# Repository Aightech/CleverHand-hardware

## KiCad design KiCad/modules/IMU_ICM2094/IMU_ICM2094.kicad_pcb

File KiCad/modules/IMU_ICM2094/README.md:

# IMU ICM2094 Module
This module is an Inertial Measurement Unit (IMU) that embeds the ICM2094 sensor. It is responsible for acquiring the acceleration, angular velocity and magnetic field signals.

## Electrical Schematic

## PCB Layout

## 3D Model

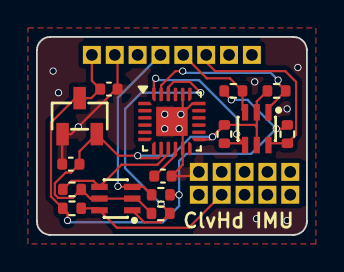
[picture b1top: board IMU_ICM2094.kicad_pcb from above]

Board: 4 copper layers, 15.0 x 11.0 mm, 34 parts (1 on the bottom side), 12 nets.

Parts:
C1, C2: 1uF; C_0402_1005Metric
C5: 100nF; C_0402_1005Metric
J1, J2, J3, J4, J5, J6, J7, J8, J9, J10, J11, J12, J13, J14, J15, J16, J17, J18: Conn_01x01_Pin; PinHeader_1x01_P1.27mm_Vertical
R1, R2, R3, R4, R5, R6, R7, R8: 4.7k; R_0402_1005Metric
U1: MCP1700T-1802E/TT; SOT-23-3_L2.9-W1.3-P1.90-LS2.4-BR
U3, U5: BSS138BKS; SOT-363_L2.1-W1.3-P0.65-LS2.3-BL
U4: ICM-20948; QFN-24-1EP_3x3mm_P0.4mm_EP1.75x1.6mm
kibuzzard-66093797: G***; kibuzzard-66093797

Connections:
+3.3V: C1.1, J1.1, R1.1, R4.1, R5.1, R8.1, U1.3 (VIN)
/1.8V: C2.1, R2.2, R3.1, R6.2, R7.1, U1.2 (VOUT), U3.2 (G2), U3.5 (G1), U4.8 (VDDIO), U4.13 (VDD), U5.2 (G2), U5.5 (G1)
/CSB: J17.1, R8.2, U5.6 (D2)
/CS_1.8V: R7.2, U4.22 (nCS), U5.1 (S2)
/MISO: J4.1, R5.2, U5.3 (D1)
/MISO_1.8V: R6.1, U4.9 (SDO/AD0), U5.4 (S1)
/MOSI: J5.1, R1.2, U3.3 (D1)
/MOSI_1.8V: R2.1, U3.4 (S1), U4.24 (SDA/SDI)
/SCK_1.8V: R3.2, U3.1 (S2), U4.23 (SCL/SCLK)
/SCLK: J6.1, R4.2, U3.6 (D2)
GND: C1.2, C2.2, C5.2, J2.1, J18.1, U1.1 (GND), U4.11 (FSYNC), U4.18 (GND), U4.20 (RESV), U4.25 (EP)
unnamed: C5.1, U4.10 (REGOUT)

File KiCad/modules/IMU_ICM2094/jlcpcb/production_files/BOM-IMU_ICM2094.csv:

Comment,Designator,Footprint,LCSC
MCP1700T-1802E/TT,U1,SOT-23-3_L2.9-W1.3-P1.90-LS2.4-BR,C150796
100nF,C5,C_0402_1005Metric,C1525
BSS138BKS,"U3,U5",SOT-363_L2.1-W1.3-P0.65-LS2.3-BL,C5224290
1uF,C2,C_0402_1005Metric,C52923
ICM-20948,U4,QFN-24-1EP_3x3mm_P0.4mm_EP1.75x1.6mm,C726001
Conn_01x01_Pin,J3,PinHeader_1x01_P1.27mm_Vertical,
Conn_01x01_Pin,J1,PinHeader_1x01_P1.27mm_Vertical,
Conn_01x01_Pin,J2,PinHeader_1x01_P1.27mm_Vertical,
Conn_01x01_Pin,J9,PinHeader_1x01_P1.27mm_Vertical,
Conn_01x01_Pin,J15,PinHeader_1x01_P1.27mm_Vertical,
Conn_01x01_Pin,J7,PinHeader_1x01_P1.27mm_Vertical,
Conn_01x01_Pin,J5,PinHeader_1x01_P1.27mm_Vertical,
Conn_01x01_Pin,J4,PinHeader_1x01_P1.27mm_Vertical,
Conn_01x01_Pin,J10,PinHeader_1x01_P1.27mm_Vertical,
Conn_01x01_Pin,J14,PinHeader_1x01_P1.27mm_Vertical,
Conn_01x01_Pin,J8,PinHeader_1x01_P1.27mm_Vertical,
Conn_01x01_Pin,J12,PinHeader_1x01_P1.27mm_Vertical,
Conn_01x01_Pin,J16,PinHeader_1x01_P1.27mm_Vertical,
Conn_01x01_Pin,J6,PinHeader_1x01_P1.27mm_Vertical,
Conn_01x01_Pin,J11,PinHeader_1x01_P1.27mm_Vertical,
Conn_01x01_Pin,J13,PinHeader_1x01_P1.27mm_Vertical,
4.7k,R1,R_0402_1005Metric,
1uF,C1,C_0402_1005Metric,
4.7k,R2,R_0402_1005Metric,
Conn_01x01_Pin,J18,PinHeader_1x01_P1.27mm_Vertical,
Conn_01x01_Pin,J17,PinHeader_1x01_P1.27mm_Vertical,
4.7k,R7,R_0402_1005Metric,
4.7k,R5,R_0402_1005Metric,
4.7k,R3,R_0402_1005Metric,
4.7k,R8,R_0402_1005Metric,
4.7k,R4,R_0402_1005Metric,
4.7k,R6,R_0402_1005Metric,

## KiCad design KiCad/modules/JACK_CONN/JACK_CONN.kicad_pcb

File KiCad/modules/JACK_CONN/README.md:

# Communication Module
This module is responsible for handling the communication between the different modules of the master node.

The communication bus is composed of :
- Power supply (3.3V) and ground
- SPI bus (MISO, MOSI, SCK)
- I2C bus (SDA, SCL)
- Address bus (A0, A1, A2, A3, A4)
- External reference voltage (AREF)

When the module is connected to the bus, it is assigned an address by the master node. This address is used to identify the module on the bus.
The communication module will will activate the chip select line of the associated sensor module when the address bus matches its address.
Additionally, each module has a unique identifier that is used to identify the module on the I2C bus.

## Electrical Schematic

## PCB Layout

## 3D Model

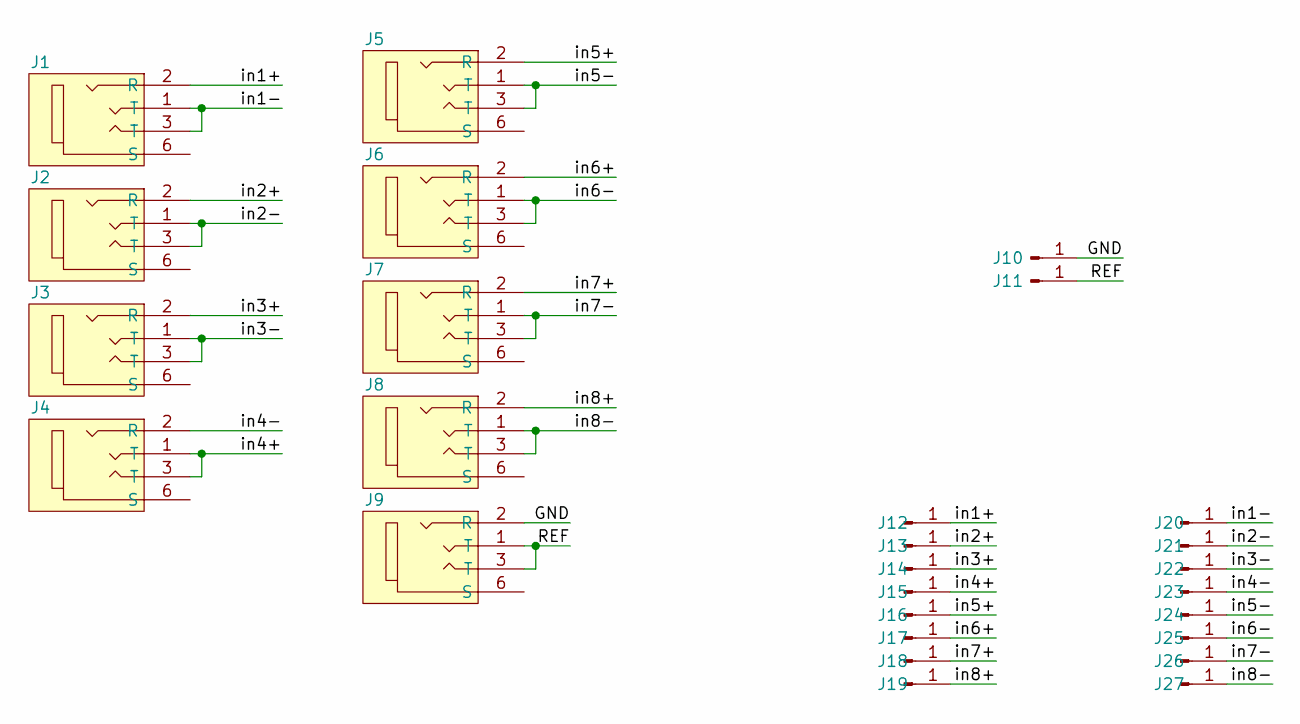
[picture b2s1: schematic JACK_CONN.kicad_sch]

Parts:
J1, J2, J3, J4, J5, J6, J7, J8, J9: jack2.5_PJ-210B; Jack_Socket_PJ-210B
J10, J11: Conn_01x01_Pin; PinHeader_1x01_P2.54mm_Vertical
J12, J13, J14, J15, J16, J17, J18, J19, J20, J21, J22, J23, J24, J25, J26, J27: Conn_01x01_Pin; Pin_D1.2mm_pogo

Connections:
/GND: J9.2 (R), J10.1
/REF: J9.1 (T), J9.3 (T), J11.1
/in1+: J1.2 (R), J12.1
/in1-: J1.1 (T), J1.3 (T), J20.1
/in2+: J2.2 (R), J13.1
/in2-: J2.1 (T), J2.3 (T), J21.1
/in3+: J3.2 (R), J14.1
/in3-: J3.1 (T), J3.3 (T), J22.1
/in4+: J4.1 (T), J4.3 (T), J15.1
/in4-: J4.2 (R), J23.1
/in5+: J5.2 (R), J16.1
/in5-: J5.1 (T), J5.3 (T), J24.1
/in6+: J6.2 (R), J17.1
/in6-: J6.1 (T), J6.3 (T), J25.1
/in7+: J7.2 (R), J18.1
/in7-: J7.1 (T), J7.3 (T), J26.1
/in8+: J8.2 (R), J19.1
/in8-: J8.1 (T), J8.3 (T), J27.1

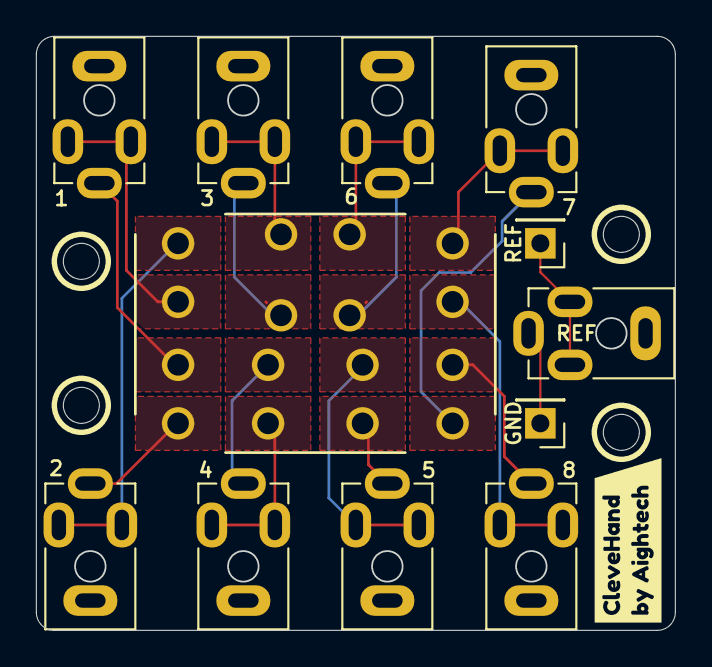
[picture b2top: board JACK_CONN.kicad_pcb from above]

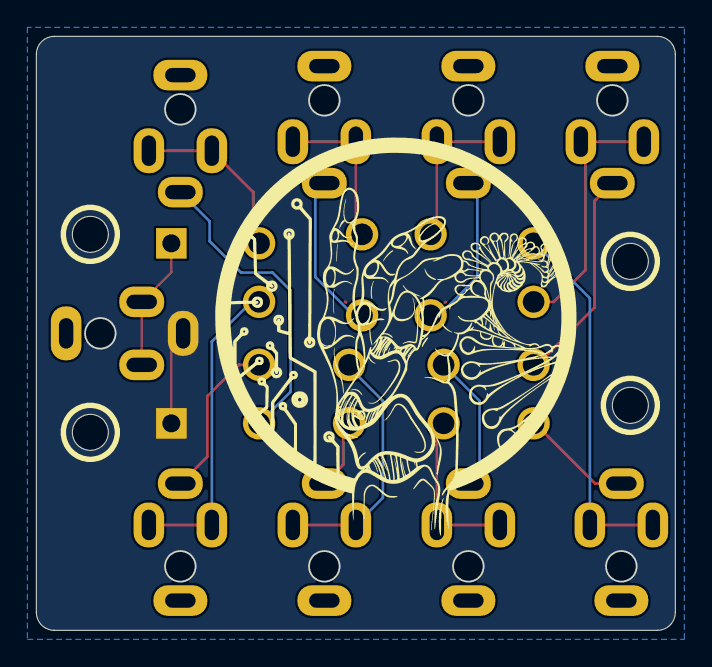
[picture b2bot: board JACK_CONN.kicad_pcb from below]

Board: 4 copper layers, 35.5 x 33.0 mm, 28 parts (16 on the bottom side), 18 nets.

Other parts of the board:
kibuzzard-6607178A: G***; kibuzzard-6607178A

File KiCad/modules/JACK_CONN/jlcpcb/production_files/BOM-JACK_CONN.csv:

Comment,Designator,Footprint,LCSC
Conn_01x01_Pin,J13,Pin_D1.2mm_pogo,
Conn_01x01_Pin,J12,Pin_D1.2mm_pogo,
Conn_01x01_Pin,J11,PinHeader_1x01_P2.54mm_Vertical,
Conn_01x01_Pin,J10,PinHeader_1x01_P2.54mm_Vertical,
jack2.5_PJ-210B,J9,Jack_Socket_PJ-210B,
Conn_01x01_Pin,J15,Pin_D1.2mm_pogo,
Conn_01x01_Pin,J14,Pin_D1.2mm_pogo,
jack2.5_PJ-210B,J6,Jack_Socket_PJ-210B,
jack2.5_PJ-210B,J3,Jack_Socket_PJ-210B,
jack2.5_PJ-210B,J1,Jack_Socket_PJ-210B,
jack2.5_PJ-210B,J4,Jack_Socket_PJ-210B,
jack2.5_PJ-210B,J2,Jack_Socket_PJ-210B,
jack2.5_PJ-210B,J5,Jack_Socket_PJ-210B,
jack2.5_PJ-210B,J7,Jack_Socket_PJ-210B,
jack2.5_PJ-210B,J8,Jack_Socket_PJ-210B,
Conn_01x01_Pin,J25,Pin_D1.2mm_pogo,
Conn_01x01_Pin,J21,Pin_D1.2mm_pogo,
Conn_01x01_Pin,J20,Pin_D1.2mm_pogo,
Conn_01x01_Pin,J18,Pin_D1.2mm_pogo,
Conn_01x01_Pin,J23,Pin_D1.2mm_pogo,
Conn_01x01_Pin,J16,Pin_D1.2mm_pogo,
Conn_01x01_Pin,J27,Pin_D1.2mm_pogo,
Conn_01x01_Pin,J24,Pin_D1.2mm_pogo,
Conn_01x01_Pin,J26,Pin_D1.2mm_pogo,
Conn_01x01_Pin,J17,Pin_D1.2mm_pogo,
Conn_01x01_Pin,J22,Pin_D1.2mm_pogo,
Conn_01x01_Pin,J19,Pin_D1.2mm_pogo,

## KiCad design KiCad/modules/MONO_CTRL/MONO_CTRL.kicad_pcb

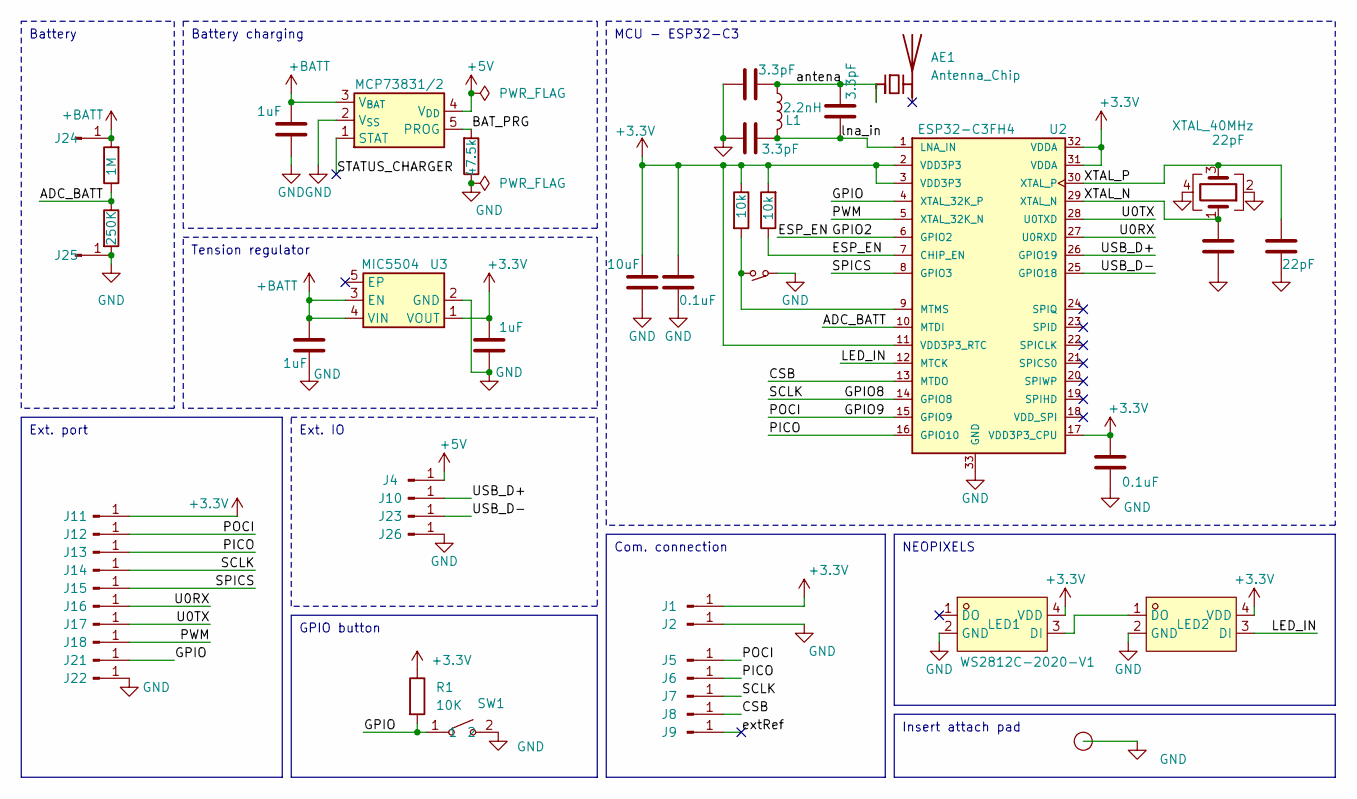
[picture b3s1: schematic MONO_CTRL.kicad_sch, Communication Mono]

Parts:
AE1: Antenna_Chip; C_1206_3216Metric; LCSC C6807751
C1, C3, C12: 3.3pF; C_0402_1005Metric
C2, C8, C9: 1uF; C_0402_1005Metric
C4: 22pF; C_0402_1005Metric; LCSC C12530
C5: 22pF; C_0402_1005Metric; LCSC C1532
C6: 10uF; C_0402_1005Metric
C7, C10: 0.1uF; C_0402_1005Metric
I1: smd_insert; insert_1.2mm
J1, J2, J4, J5, J6, J7, J8, J9, J10, J11, J12, J13, J14, J15, J16, J17, J18, J21, J22, J23, J24, J25, J26: Conn_01x01_Pin; PinHeader_1x01_P1.27mm_Vertical
L1: 2.2nH; L_0402_1005Metric
LED1: WS2812C-2020-V1; LED-SMD_4P-L2.0-W2.0-TL_WS2812B-2020; LCSC Part C2976072
LED2: WS2812C; LED-SMD_4P-L2.0-W2.0-TL_WS2812B-2020; LCSC Part C2976072
R1: 10K; R_0402_1005Metric; LCSC C25744
R2: 47.5k; R_0402_1005Metric; LCSC C25762
R3: 1M; R_0402_1005Metric; LCSC C25762
R4, R5: 10k; R_0402_1005Metric; LCSC C25762
R6: 250K; R_0402_1005Metric; LCSC C25762
SW1: TS-1088R-02026; SW-SMD_L3.9-W3.0-P4.45; LCSC Part C455280
SW2: SW-SMD_L3.9-W3.0-P4.45; LCSC C720477
U1: MCP73831/2; SOT-23-5; LCSC C14879
U2: ESP32-C3FH4; PARTREV V1.0; LCSC C2858491
U3: MIC5504; UDFN-4-1EP_1x1mm_P0.65mm_EP0.48x0.48mm; LCSC C3021135
Y1: XTAL_40MHz; Crystal_SMD_2016-4Pin_2.0x1.6mm; LCSC C2929402

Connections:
+3.3V: C6.1, C7.1, C9.1, C10.1, J1.1, J11.1, LED1.4 (VDD), LED2.4 (VDD), R1.1, R4.1, R5.2, U2.2 (VDD3P3), U2.3 (VDD3P3), U2.11 (VDD3P3_RTC), U2.17 (VDD3P3_CPU), U2.31 (VDDA), U2.32 (VDDA), U3.1 (VOUT)
+5V: J4.1, U1.4 (V_{DD})
+BATT: C2.1, C8.1, J24.1, R3.2, U1.3 (V_{BAT}), U3.3 (EN), U3.4 (VIN)
/ADC_BATT: R3.1, R6.1, U2.10 (MTDI)
/BAT_PRG: R2.2, U1.5 (PROG)
/CSB: J8.1, U2.13 (MTDO)
/ESP_EN: R5.1, U2.6 (GPIO2), U2.7 (CHIP_EN)
/GPIO: J21.1, R1.2, SW1.1, U2.4 (XTAL_32K_P)
/GPIO8: J7.1, J14.1, U2.14 (GPIO8)
/GPIO9: J5.1, J12.1, U2.15 (GPIO9)
/LED_IN: LED2.3 (DI), U2.12 (MTCK)
/PICO: J6.1, J13.1, U2.16 (GPIO10)
/PWM: J18.1, U2.5 (XTAL_32K_N)
/SPICS: J15.1, U2.8 (GPIO3)
/STATUS_CHARGER: U1.1 (STAT)
/U0RX: J16.1, U2.27 (U0RXD)
/U0TX: J17.1, U2.28 (U0TXD)
/USB_D+: J10.1, U2.26 (GPIO19)
/USB_D-: J23.1, U2.25 (GPIO18)
/XTAL_N: C4.1, U2.29 (XTAL_N), Y1.1
/XTAL_P: C5.1, U2.30 (XTAL_P), Y1.3
/antena: AE1.1 (FEED), C1.1, C12.1, L1.1
/extRef: J9.1
/lna_in: C3.1, C12.2, L1.2, U2.1 (LNA_IN)
GND: C1.2, C2.2, C3.2, C4.2, C5.2, C6.2, C7.2, C8.2, C9.2, C10.2, I1.1 (conn), J2.1, J22.1, J25.1, J26.1, LED1.2 (GND), LED2.2 (GND), R2.1, R6.2, SW1.2, SW2.1, U1.2 (V_{SS}), U2.33 (GND), U3.2 (GND), Y1.2, Y1.4
unnamed: LED1.3 (DI), LED2.1 (DO)
unnamed: R4.2, SW2.2, U2.9 (MTMS)

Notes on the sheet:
Battery charging
Insert attach pad
NEOPIXELS
MCU - ESP32-C3
Com. connection
GPIO button
Tension regulator
Battery
Ext. IO
Ext. port

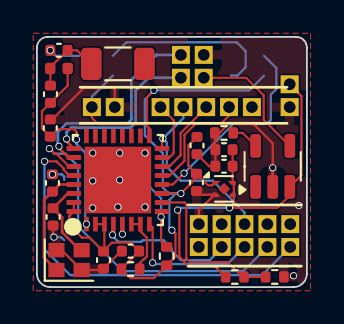
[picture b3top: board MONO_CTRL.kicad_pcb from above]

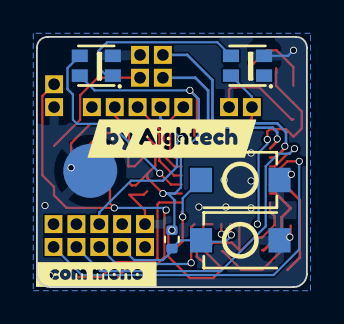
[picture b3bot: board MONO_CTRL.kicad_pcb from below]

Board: 4 copper layers, 15.0 x 13.9 mm, 53 parts (8 on the bottom side), 25 nets.

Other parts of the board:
kibuzzard-66D6133A: G***; kibuzzard-66D6133A
kibuzzard-658C2757: G***; kibuzzard-658C2757

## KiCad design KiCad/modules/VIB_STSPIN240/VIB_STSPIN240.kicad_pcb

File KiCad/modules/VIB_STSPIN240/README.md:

# Vibrotactile STSPIN240 Module
This module is a vibrotactile module that embeds the STSPIN240 motor driver. It is responsible for generating the vibrotactile signals that will be sent to the vibrotactile actuators.

## Electrical Schematic

## PCB Layout

## 3D Model

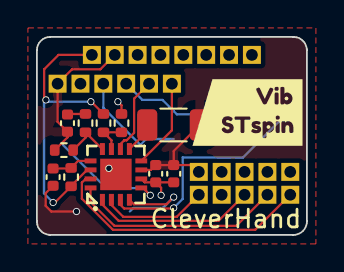
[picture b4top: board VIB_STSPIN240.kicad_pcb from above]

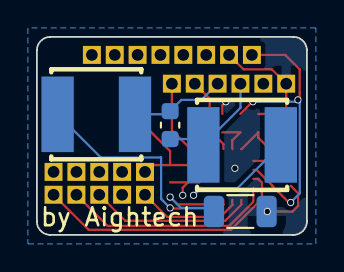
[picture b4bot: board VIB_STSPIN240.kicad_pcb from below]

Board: 4 copper layers, 15.0 x 11.0 mm, 40 parts (4 on the bottom side), 19 nets.

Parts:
C3: 2.2uF; C_0402_1005Metric
C4: 22uF; C_0402_1005Metric
C5: 22nF; C_0402_1005Metric
C6: 10nF; C_0402_1005Metric
C7: 2.2uF - 16V ceramic X7R; C_0603_1608Metric
J1, J2, J3, J4, J5, J6, J7, J8, J9, J10, J11, J12, J13, J14, J15, J16, J17, J18, J19, J20, J21, J22, J23, J24: Conn_01x01_Pin; PinHeader_1x01_P1.27mm_Vertical
L1, L2: FNR5040S330MT; IND-SMD_L5.0-W5.0_FNR50XXS
R1, R2: 0.33; R_1206_3216Metric
R3, R6, R7: 1k; R_0402_1005Metric
R4: 47k; R_0402_1005Metric
R5: 18k; R_0402_1005Metric
U3: STSPIN240; QFN-16_L3.0-W3.0-P0.50-BL-EP1.7
kibuzzard-66089A17: G***; kibuzzard-66089A17

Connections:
+3.3V: J1.1, R5.2, R6.1, U3.14 (STBY\RESET)
/AIN0: J16.1, U3.2 (PWMA)
/I2C_SDA: J15.1, U3.15 (PHB)
/OA1: L1.2, U3.3 (OUTA1)
/OA2: L2.2, U3.5 (OUTA2)
/OB1: J21.1, U3.10 (OUTB1)
/OB2: J22.1, U3.8 (OUTB2)
/OUTA1: C7.1, J19.1, L1.1
/OUTA2: C7.2, J20.1, L2.1
/SPICS_ARM: J13.1, U3.1 (PHA)
/Vref: R6.2, R7.1, U3.11 (REF)
/i2C_SCL: J14.1, U3.16 (PWMB)
/senseA: R1.2, U3.4 (SENSEA)
/senseB: R2.1, U3.9 (SENSEB)
/toff: R3.1, R4.1, U3.12 (TOFF)
GND: C3.2, C4.2, C5.2, C6.2, J2.1, J18.1, J24.1, R1.1, R2.2, R4.2, R7.2, U3.7 (GND), U3.17 (GND)
unnamed: C5.1, R3.2
unnamed: C6.1, R5.1, U3.13 (EN\FAULT)
VCC: C3.1, C4.1, J23.1, U3.6 (VS)

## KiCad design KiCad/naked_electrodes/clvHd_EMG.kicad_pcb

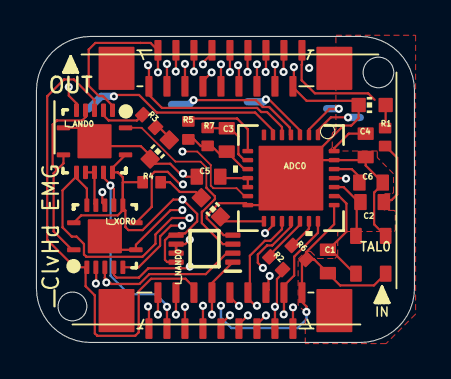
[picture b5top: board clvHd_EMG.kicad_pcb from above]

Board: 4 copper layers, 21.0 x 17.0 mm, 25 parts (0 on the bottom side), 37 nets.

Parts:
@HOLE0, @HOLE1: (no value)
ADC0: ADS1293CISQ/NOPB; RSG28_3P6X3P6_TEX
C1, C2: 22pF; C0402
C3: 1nF; C0402
C4, C5: 100nF; C0402
C6: 1uF; C0402
L1: Green; CHIP-LED0603
L2: Red; CHIP-LED0603
L3: White; CHIP-LED0603
L_AND0: SN74ALVC08; VQFN-14-CUSTOM
L_NAND0: SN74AUP2G00; VSSOP
L_XOR0: SN74LVC86; VQFN-14-CUSTOM
R1, R2, R3, R4: 51; R0402
R5: 10k; R0402
R6: 1M; R0402
R7: 10M; R0402
TAL0: C387328; SMD-3225_4P
UNK1, UNK2: X05C2018TZ

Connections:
A0: L_AND0.12, L_XOR0.10, UNK1.3
A1: L_AND0.9, L_XOR0.13, UNK1.5
A2: L_AND0.4, L_XOR0.2, UNK1.6
A3: L_NAND0.1, L_XOR0.5, UNK1.8
ALARMB: ADC0.15, L2.C
CLK: ADC0.21, UNK1.16, UNK2.3
CMOUT: ADC0.8, R5.1
CS: ADC0.16, L_NAND0.6, L_NAND0.7
DIN: ADC0.18, UNK1.13, UNK2.6
DOUT: R2.2, UNK1.15, UNK2.4
DRDYB: ADC0.20, R6.1
GND: ADC0.14, ADC0.27, ADC0.29, C4.2, C5.2, C6.2, L1.C, L3.C, L_AND0.7, L_AND0.15, L_NAND0.4, L_XOR0.7, L_XOR0.15, TAL0.2, UNK1.4, UNK1.7, UNK1.11, UNK1.14, UNK1.17, UNK2.2, UNK2.5, UNK2.8, UNK2.12, UNK2.15
GPIO1: L_AND0.2, UNK1.2, UNK2.17
IN5: ADC0.5, UNK1.1, UNK2.18
unnamed: L_AND0.1, L_NAND0.3
unnamed: L1.A, R1.2
unnamed: ADC0.19, R2.1
unnamed: ADC0.23, C1.2, TAL0.4
unnamed: L_AND0.3, R3.2
unnamed: L2.A, R4.1
unnamed: L3.A, R3.1
unnamed: ADC0.24, C2.2, TAL0.3
unnamed: ADC0.26, C6.1
unnamed: L_AND0.10, L_AND0.11, L_XOR0.12
unnamed: L_AND0.5, L_AND0.8, L_XOR0.1
unnamed: ADC0.10, C3.1, R5.2, R7.2
unnamed: L_AND0.6, L_NAND0.2, L_XOR0.4
RLDOUT: ADC0.9, C3.2, R7.1
RLDREF: ADC0.11, ADC0.12, C5.1
RST: ADC0.25, UNK1.9, UNK2.10
S0: L_XOR0.8, UNK2.16
S1: L_XOR0.11, UNK2.14
S2: L_XOR0.3, UNK2.13
S3: L_XOR0.6, UNK2.11
SCLK: ADC0.17, UNK1.12, UNK2.7
SYNCB: ADC0.13, UNK1.10, UNK2.9
VDD: ADC0.22, ADC0.28, C1.1, C2.1, C4.1, L_AND0.13, L_AND0.14, L_NAND0.5, L_NAND0.8, L_XOR0.9, L_XOR0.14, R1.1, R4.2, R6.2, TAL0.1, UNK1.18, UNK2.1

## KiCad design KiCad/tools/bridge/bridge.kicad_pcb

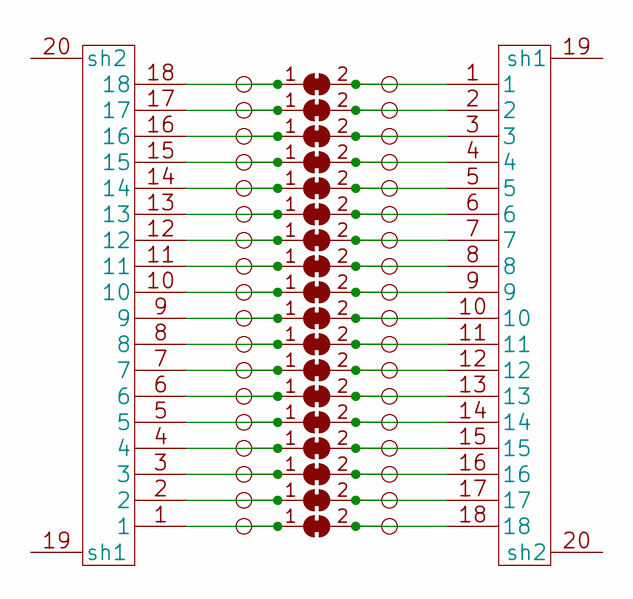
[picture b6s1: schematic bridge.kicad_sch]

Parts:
J1, J2: XF2J-1824-12A; LCSC C397324
JP1: SolderJumper_2_Bridged
JP2, JP3, JP4, JP5, JP6, JP7, JP8, JP9, JP10, JP11, JP12, JP13, JP14, JP15, JP16, JP17, JP18: SolderJumper_2_Bridged; SolderJumper-2_P1.3mm_Bridged_RoundedPad1.0x1.5mm
TP1: TestPoint
TP2, TP3, TP4, TP5, TP6, TP7, TP8, TP9, TP10, TP11, TP12, TP13, TP14, TP15, TP16, TP17, TP18, TP19, TP20, TP21, TP22, TP23, TP24, TP25, TP26, TP27, TP28, TP29, TP30, TP31, TP32, TP33, TP34, TP35, TP36: TestPoint; Pin_D0.7mm_L6.5mm_W1.8mm_FlatFork

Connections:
unnamed: J1.18, JP1.1 (A), TP1.1
unnamed: J2.1, JP1.2 (B), TP19.1
unnamed: J1.17, JP2.1 (A), TP2.1
unnamed: J2.2, JP2.2 (B), TP20.1
unnamed: J1.16, JP3.1 (A), TP3.1
unnamed: J2.3, JP3.2 (B), TP21.1
unnamed: J1.15, JP4.1 (A), TP4.1
unnamed: J2.4, JP4.2 (B), TP22.1
unnamed: J1.14, JP5.1 (A), TP5.1
unnamed: J2.5, JP5.2 (B), TP23.1
unnamed: J1.13, JP6.1 (A), TP6.1
unnamed: J2.6, JP6.2 (B), TP24.1
unnamed: J1.12, JP7.1 (A), TP7.1
unnamed: J2.7, JP7.2 (B), TP25.1
unnamed: J1.11, JP8.1 (A), TP8.1
unnamed: J2.8, JP8.2 (B), TP26.1
unnamed: J1.10, JP9.1 (A), TP9.1
unnamed: J2.9, JP9.2 (B), TP27.1
unnamed: J1.9, JP10.1 (A), TP10.1
unnamed: J2.10, JP10.2 (B), TP28.1
unnamed: J1.8, JP11.1 (A), TP11.1
unnamed: J2.11, JP11.2 (B), TP29.1
unnamed: J1.7, JP12.1 (A), TP12.1
unnamed: J2.12, JP12.2 (B), TP30.1
unnamed: J1.6, JP13.1 (A), TP13.1
unnamed: J2.13, JP13.2 (B), TP31.1
unnamed: J1.5, JP14.1 (A), TP14.1
unnamed: J2.14, JP14.2 (B), TP32.1
unnamed: J1.4, JP15.1 (A), TP15.1
unnamed: J2.15, JP15.2 (B), TP33.1
unnamed: J1.3, JP16.1 (A), TP16.1
unnamed: J2.16, JP16.2 (B), TP34.1
unnamed: J1.2, JP17.1 (A), TP17.1
unnamed: J2.17, JP17.2 (B), TP35.1
unnamed: J1.1, JP18.1 (A), TP18.1
unnamed: J2.18, JP18.2 (B), TP36.1

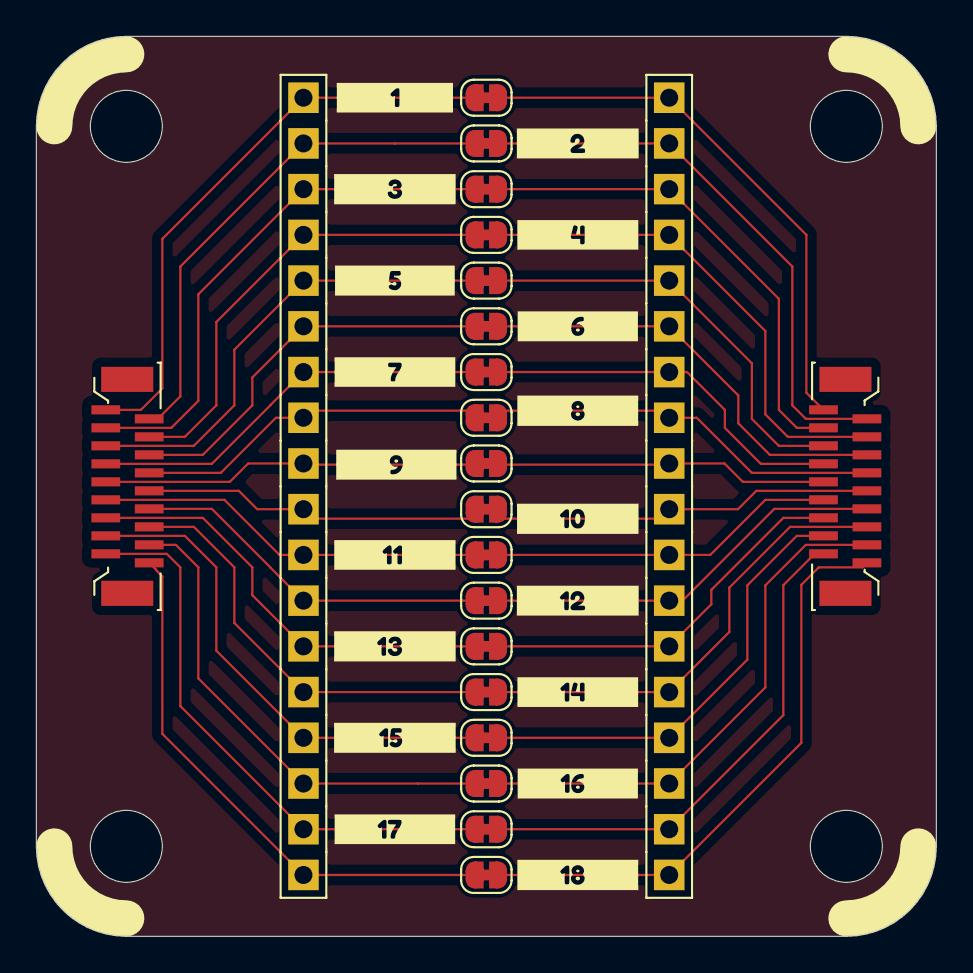
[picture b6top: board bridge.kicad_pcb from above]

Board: 4 copper layers, 50.0 x 50.0 mm, 74 parts (0 on the bottom side), 36 nets.

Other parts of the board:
kibuzzard-63B56CBF: G***; kibuzzard-63B56CBF
kibuzzard-63B56D3C: G***; kibuzzard-63B56D3C
kibuzzard-63B56D06: G***; kibuzzard-63B56D06
kibuzzard-63B56D6D: G***; kibuzzard-63B56D6D
kibuzzard-63B56D79: G***; kibuzzard-63B56D79
kibuzzard-63B56EBC: G***; kibuzzard-63B56EBC
kibuzzard-63B56EF1: G***; kibuzzard-63B56EF1
kibuzzard-63B56F8D: G***; kibuzzard-63B56F8D
kibuzzard-63B56F28: G***; kibuzzard-63B56F28
kibuzzard-63B56F37: G***; kibuzzard-63B56F37
kibuzzard-63B56F80: G***; kibuzzard-63B56F80
kibuzzard-63B56F84: G***; kibuzzard-63B56F84
kibuzzard-63B56F93: G***; kibuzzard-63B56F93
kibuzzard-63B56FB5: G***; kibuzzard-63B56FB5
kibuzzard-63B56FC4: G***; kibuzzard-63B56FC4
kibuzzard-63B56FCC: G***; kibuzzard-63B56FCC
kibuzzard-63B56FD6: G***; kibuzzard-63B56FD6
kibuzzard-63B56FE1: G***; kibuzzard-63B56FE1

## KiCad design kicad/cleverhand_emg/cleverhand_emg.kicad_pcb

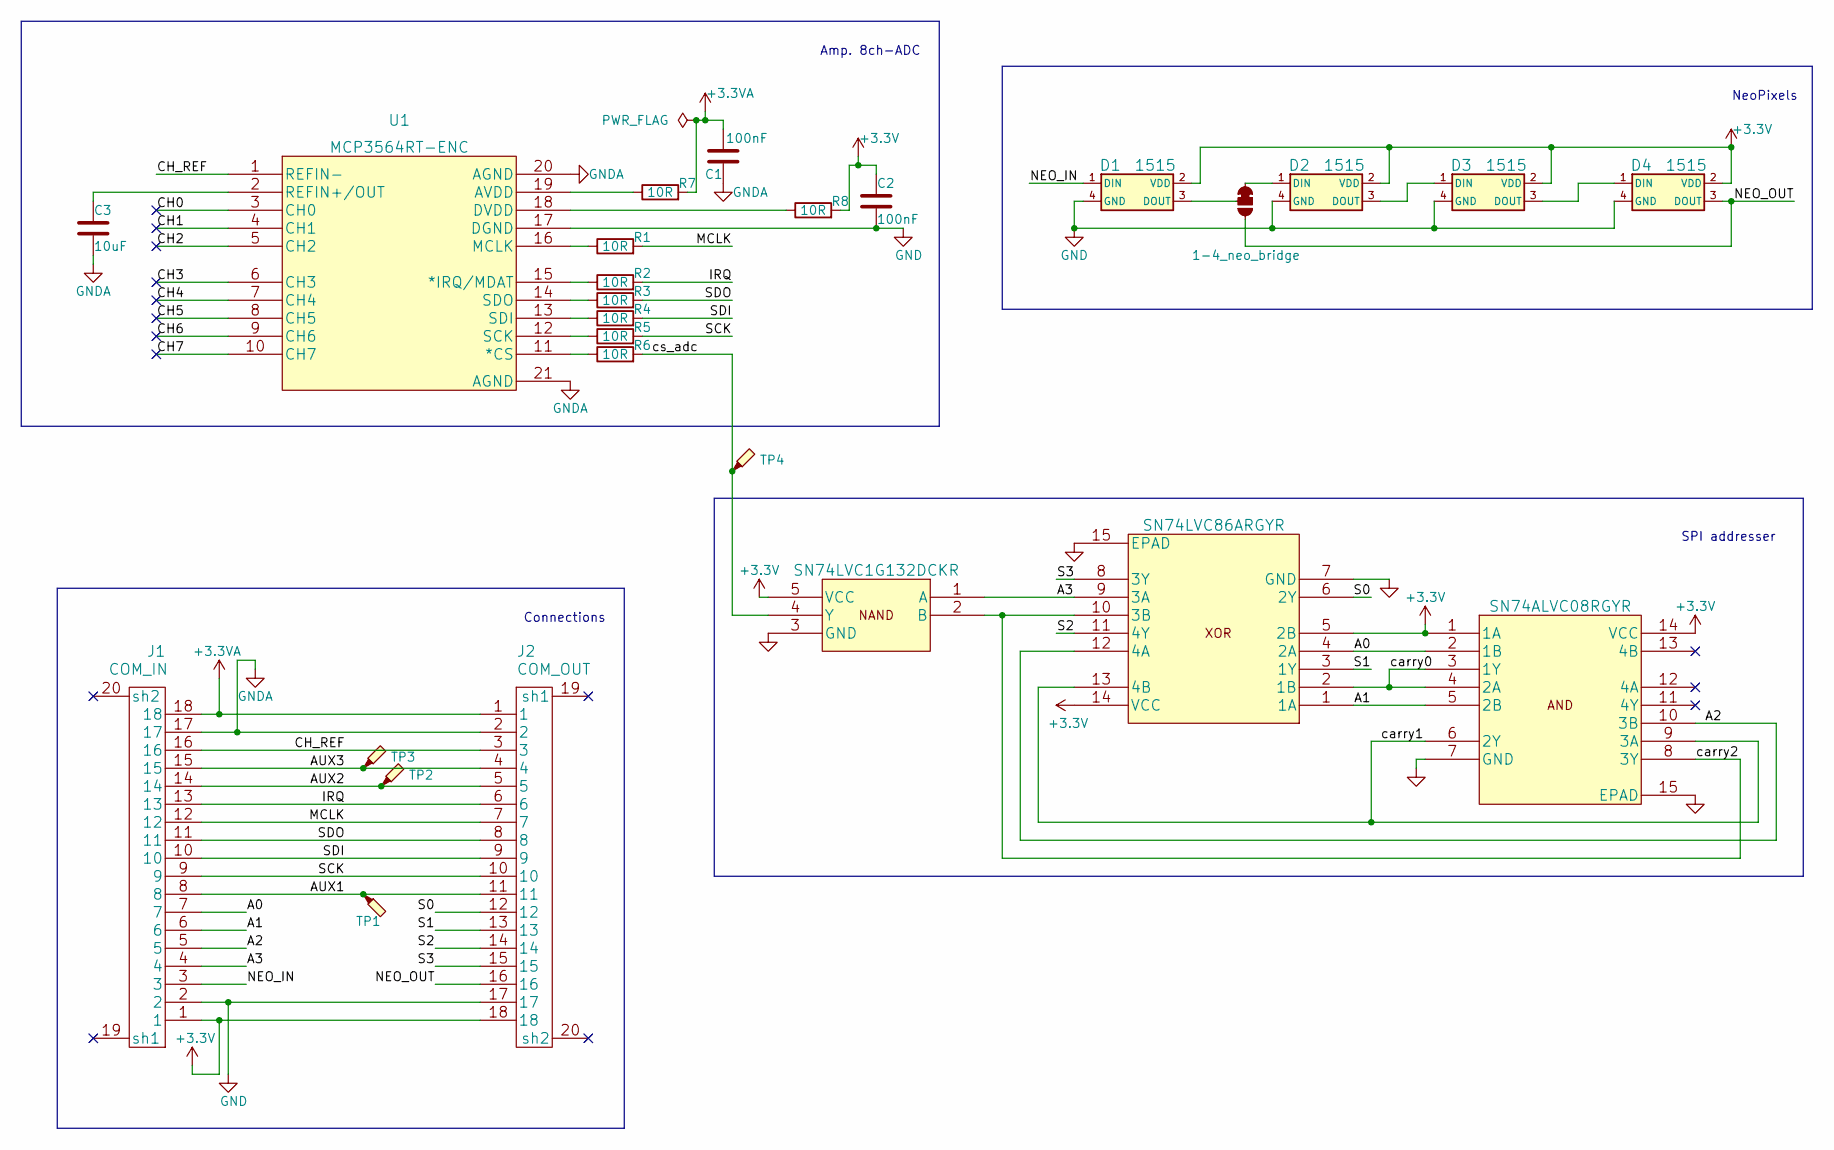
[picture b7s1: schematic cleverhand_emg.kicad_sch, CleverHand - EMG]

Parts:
C1, C2: 100nF; C_0402_1005Metric
C3: 10uF; C_0402_1005Metric
D1, D2, D3, D4: 1515; neopixel_1515
J1: COM_IN; XF2J-1824-12A
J2: COM_OUT; XF2J-1824-12A
JP1: 1-4_neo_bridge; SolderJumper-3_P1.3mm_Bridged12_RoundedPad1.0x1.5mm_NumberL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
R1, R2, R3, R4, R5, R6, R7, R8: 10R; R_0402_1005Metric
TP1, TP2, TP4: TestPoint_Probe; TestPoint_Pad_D1.0mm
TP3: TestPoint_Probe
U1: MCP3564RT-ENC; MCP3564RT-E&slash_NC
U2: SN74LVC86ARGYR
U4: SN74ALVC08RGYR
U5: SN74LVC1G132DCKR

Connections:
+3.3V: C2.1, D1.2 (VDD), D2.2 (VDD), D3.2 (VDD), D4.2 (VDD), J1.1, J2.18, R8.2, U2.5 (2B), U2.14 (VCC), U4.1 (1A), U4.14 (VCC), U5.5 (VCC)
+3.3VA: C1.2, J1.18, J2.1, R7.2
/A0: J1.7, U2.4 (2A), U4.2 (1B)
/A1: J1.6, U2.1 (1A), U4.5 (2B)
/A2: J1.5, U2.12 (4A), U4.10 (3B)
/A3: J1.4, U2.9 (3A), U5.1 (A)
/AUX1: J1.8, J2.11, TP1.1
/AUX2: J1.14, J2.5, TP2.1
/AUX3: J1.15, J2.4, TP3.1
/CH0: U1.3 (CH0)
/CH1: U1.4 (CH1)
/CH2: U1.5 (CH2)
/CH3: U1.6 (CH3)
/CH4: U1.7 (CH4)
/CH5: U1.8 (CH5)
/CH6: U1.9 (CH6)
/CH7: U1.10 (CH7)
/CH_REF: J1.16, J2.3, U1.1 (REFIN-)
/IRQ: J1.13, J2.6, R2.2
/MCLK: J1.12, J2.7, R1.2
/NEO_IN: D1.1 (DIN), J1.3
/NEO_OUT: D4.3 (DOUT), J2.16, JP1.3 (B)
/S0: J2.12, U2.6 (2Y)
/S1: J2.13, U2.3 (1Y)
/S2: J2.14, U2.11 (4Y)
/S3: J2.15, U2.8 (3Y)
/SCK: J1.9, J2.10, R5.2
/SDI: J1.10, J2.9, R4.2
/SDO: J1.11, J2.8, R3.2
/carry0: U2.2 (1B), U4.3 (1Y), U4.4 (2A)
/carry1: U2.13 (4B), U4.6 (2Y), U4.9 (3A)
/carry2: U2.10 (3B), U4.8 (3Y), U5.2 (B)
/cs_adc: R6.2, TP4.1, U5.4 (Y)
GND: C2.2, D1.4 (GND), D2.4 (GND), D3.4 (GND), D4.4 (GND), J1.2, J2.17, U1.17 (DGND), U2.7 (GND), U2.15 (EPAD), U4.7 (GND), U4.15 (EPAD), U5.3 (GND)
GNDA: C1.1, C3.2, J1.17, J2.2, U1.20 (AGND), U1.21 (AGND)
unnamed: C3.1, U1.2 (REFIN+/OUT)
unnamed: D1.3 (DOUT), JP1.2 (C)
unnamed: D2.1 (DIN), JP1.1 (A)
unnamed: D2.3 (DOUT), D3.1 (DIN)
unnamed: D3.3 (DOUT), D4.1 (DIN)
unnamed: R1.1, U1.16 (MCLK)
unnamed: R2.1, U1.15 (*IRQ/MDAT)
unnamed: R3.1, U1.14 (SDO)
unnamed: R4.1, U1.13 (SDI)
unnamed: R5.1, U1.12 (SCK)
unnamed: R6.1, U1.11 (*CS)
unnamed: R7.1, U1.19 (AVDD)
unnamed: R8.1, U1.18 (DVDD)

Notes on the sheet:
Connections
SPI addresser
Amp. 8ch-ADC
NeoPixels

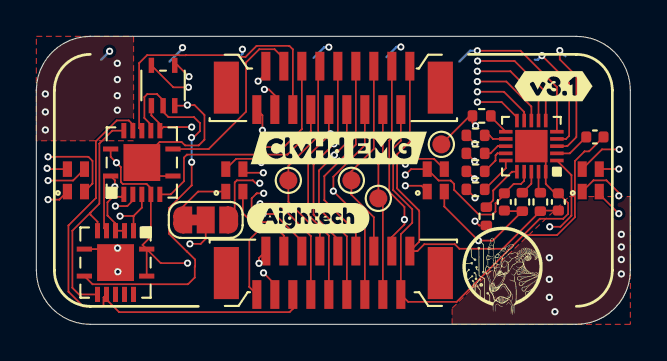
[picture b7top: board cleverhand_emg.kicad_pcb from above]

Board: 4 copper layers, 33.0 x 16.0 mm, 29 parts (0 on the bottom side), 40 nets.

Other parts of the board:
kibuzzard-6360EE7B: G***; kibuzzard-6360EE7B
kibuzzard-6360EEA9: G***; kibuzzard-6360EEA9
kibuzzard-6360F8A7: G***; kibuzzard-6360F8A7
